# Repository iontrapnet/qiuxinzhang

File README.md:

# qiuxinzhang
zhang qiuxin 
qiuxin@ruc.edu.cn

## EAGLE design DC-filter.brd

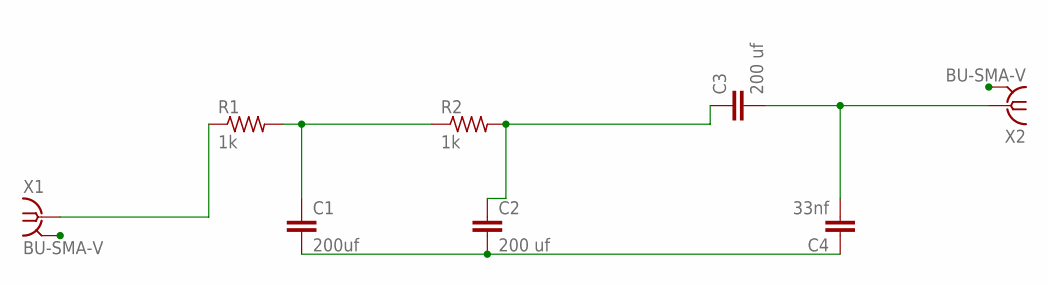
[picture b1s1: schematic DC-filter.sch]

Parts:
C1: 200uf; C1310
C2, C3: 200 uf; C1310
C4: 33nf; C1310
R1, R2: 1k; 0204/7
X1, X2: BU-SMA-V

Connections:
GND: X1.2, X1.3 (2), X1.4 (2), X1.5 (2), X2.2, X2.3 (2), X2.4 (2), X2.5 (2)
unnamed: R1.1, X1.1
unnamed: C1.1, R1.2, R2.1
unnamed: C2.1, C3.1, R2.2
unnamed: C3.2, C4.2, X2.1
unnamed: C1.2, C2.2, C4.1

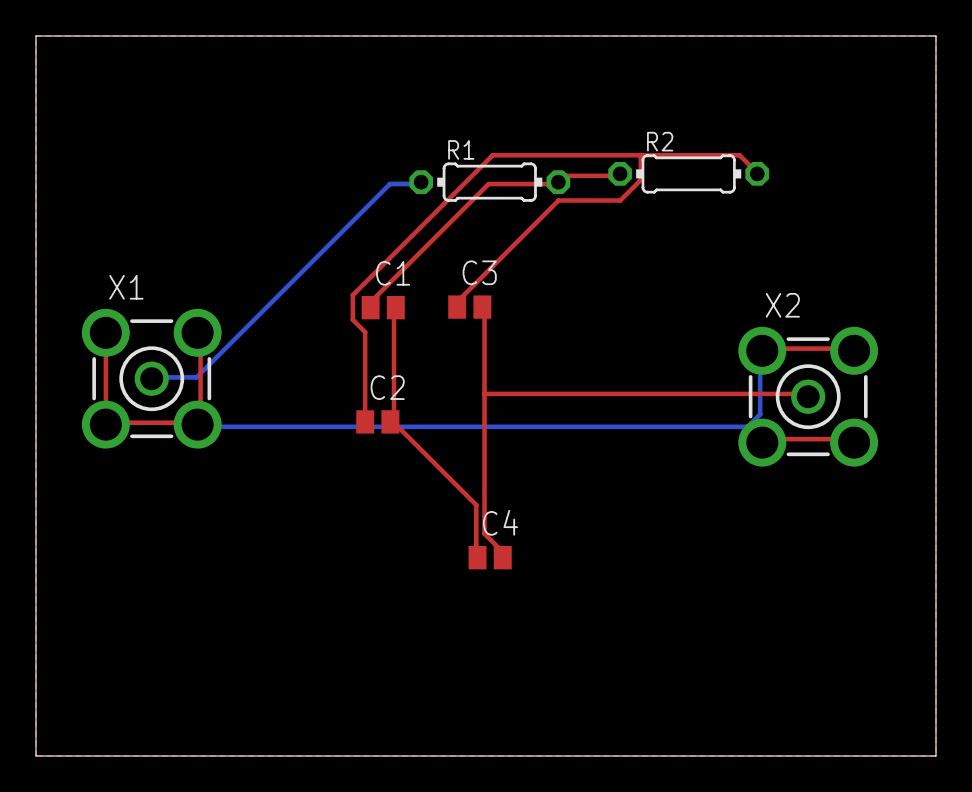
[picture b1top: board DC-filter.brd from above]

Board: 2 copper layers, 50.0 x 40.0 mm, 8 parts (0 on the bottom side), 6 nets.

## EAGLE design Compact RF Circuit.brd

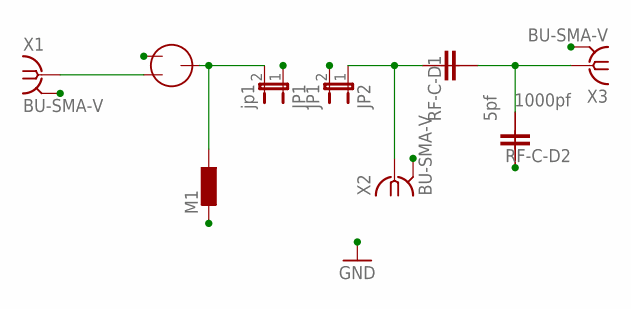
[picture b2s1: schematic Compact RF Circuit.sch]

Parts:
JP1: jp1; JP1
JP2: JP1
M1: L; L1812
M2: ADJ-CAPACITORS9328-1; 9328
RF-C-D1: 5pf; 2220
RF-C-D2: 1000pf; 2220
X1, X2, X3: BU-SMA-V

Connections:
GND: JP1.1, JP2.2, M1.2, M2.P$1 (1), RF-C-D2.P$1 (1), X1.2, X1.3 (2), X1.4 (2), X1.5 (2), X2.2, X2.3 (2), X2.4 (2), X2.5 (2), X3.2, X3.3 (2), X3.4 (2), X3.5 (2)
unnamed: M2.P$2 (2), X1.1
unnamed: JP1.2, M1.1, M2.P$3 (3)
unnamed: JP2.1, RF-C-D1.P$1 (1), X2.1
unnamed: RF-C-D1.P$2 (2), RF-C-D2.P$2 (2), X3.1

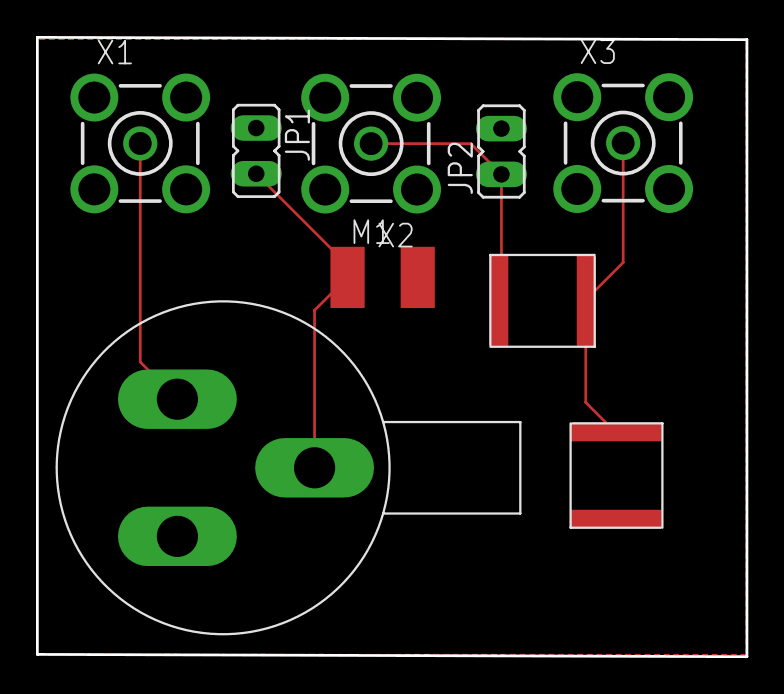
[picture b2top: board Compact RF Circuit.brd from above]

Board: 2 copper layers, 39.4 x 34.4 mm, 9 parts (0 on the bottom side), 5 nets.

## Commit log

2018-01-19 Create DC-filter
